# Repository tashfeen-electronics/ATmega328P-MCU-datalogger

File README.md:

# ATmega328P Data Logger — EEPROM + RTC

A compact, standalone data logging system built around the **ATmega328P** microcontroller, featuring **non-volatile EEPROM storage** and a **real-time clock (RTC)** for accurate timestamping. Designed for reliable, low-power, long-duration data collection without needing a constant computer connection.

---

## 🧠 Overview

This project logs sensor readings at fixed intervals, timestamps each entry using an RTC module, and stores the data permanently in EEPROM — surviving power loss, resets, and disconnects. It's built as a foundation for embedded data acquisition systems that need to run unattended in the field.

---

## ⚙️ Features

- 📌 Real-time timestamping using an external RTC module
- 💾 Persistent storage via EEPROM (data survives power cycles)
- 🔁 Configurable logging interval
- 🔋 Low power design, suitable for battery-powered deployment
- 📤 Simple data retrieval for post-processing and analysis
- 🧩 Modular code structure — easy to extend with new sensors

---

## 🛠️ Hardware Used

| Component            | Purpose                          |
|-----------------------|-----------------------------------|
| ATmega328P            | Core microcontroller / logic unit |
| RTC Module DS1337S    | Real-time timestamping   |
| EEPROM (external/internal) | Non-volatile data storage     |
| Sensor(s)              | Data source (analog/digital)     |
| Power supply / battery | Field-deployable operation       |

---

## 🧩 System Architecture

```
[ Sensor ] → [ ATmega328P ] → [ RTC: Timestamp ] → [ EEPROM: Store ]
                                      ↓
                              [ Data Retrieval / Analysis ]
```

**Flow:**
1. The MCU wakes up (or runs continuously) and triggers a reading at a set interval.
2. The RTC module provides the current date and time.
3. Sensor data is paired with the timestamp.
4. The combined record is written to EEPROM at the next available memory address.
5. Data can later be read out via serial interface for analysis.

---

## 📝 Design Notes

- **Memory management:** EEPROM write cycles are limited (~100,000 per cell), so writes are spaced out and address pointers are tracked to avoid unnecessary wear and overwrites.
- **Timestamp accuracy:** The RTC module runs independently of the MCU clock, so logged times remain accurate even after resets or brief power loss (backed by a coin-cell battery).
- **Data structure:** Each log entry is packed into a fixed-size record (timestamp + sensor value) to keep read/write operations predictable and efficient.
- **Power efficiency:** Sleep modes are used between logging intervals to minimize current draw for battery-powered, long-term deployments.
- **Scalability:** The logging interval, sensor type, and storage size are all designed to be easily reconfigurable without restructuring the core logic.

---

## 🚀 Practical Applications

- 🌱 **Agriculture** — soil moisture / temperature logging for irrigation planning
- 🌡️ **Environmental monitoring** — tracking temperature, humidity, or air quality over time
- 🏭 **Industrial systems** — recording equipment performance for predictive maintenance
- 🔬 **Research & academic projects** — collecting reliable, timestamped datasets in the field
- 🏠 **Home automation** — logging conditions for smart, data-driven decisions

---

## 📂 Data Retrieval

Logged data can be read out via the serial interface and exported for analysis in tools like Excel, Python (pandas), or MATLAB — enabling trend analysis, visualization, and further processing.

---

## 🔮 Future Improvements

- SD card integration for larger-scale storage
- Wireless data transmission (e.g. via ESP module)
- Multi-sensor support with dynamic record formatting
- Low-power sleep/wake scheduling for extended battery life

---

## 📜 License

This project is open for learning, modification, and reuse. Feel free to fork, build on it, and share improvements.

---

**Built as part of ongoing exploration in embedded systems and circuit design.**

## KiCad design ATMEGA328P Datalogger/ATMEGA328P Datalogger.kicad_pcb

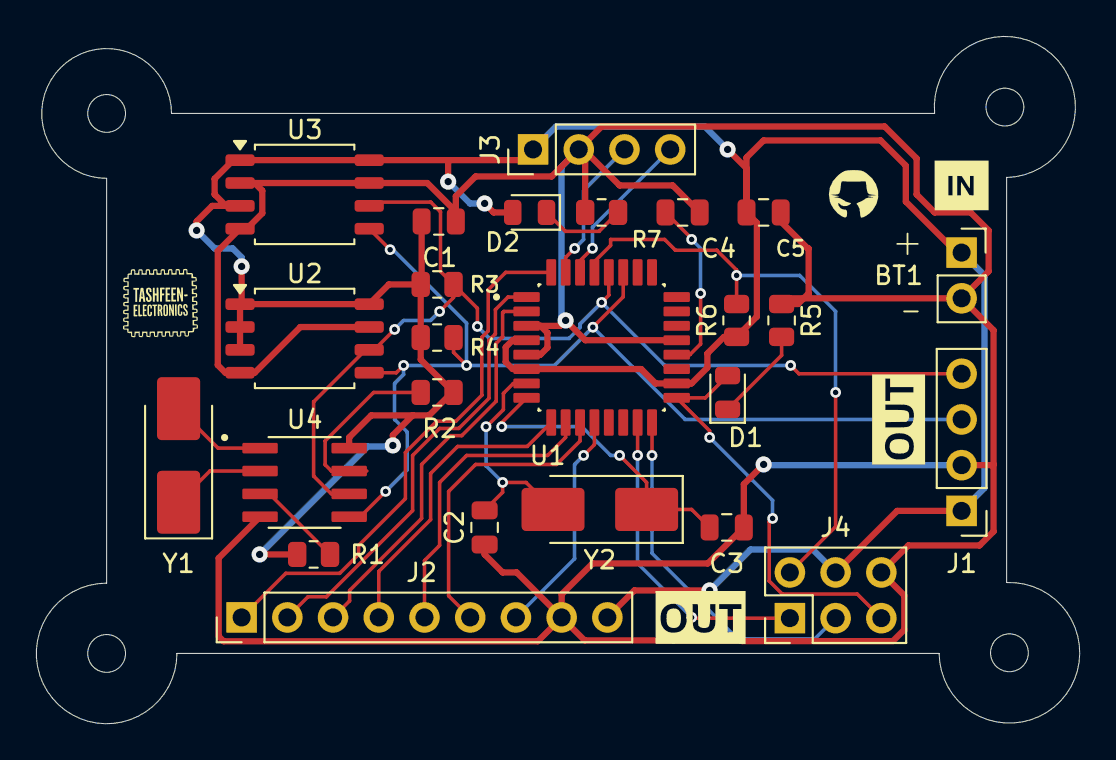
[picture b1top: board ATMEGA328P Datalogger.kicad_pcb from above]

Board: 2 copper layers, 58.0 x 38.2 mm, 30 parts (1 on the bottom side), 26 nets.

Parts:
.: LOGO
BT1: Battery; PinSocket_1x02_P2.54mm_Vertical
C1, C4: 0.1u; C_0805_2012Metric
C2, C3: 22p; C_0805_2012Metric
C5: 100n; C_0805_2012Metric
D1, D2: LED; LED_0805_2012Metric
H1, H2, H3, H4: MountingHole; MountingHole_2.1mm
J1, J3: Conn_01x04_Pin; PinHeader_1x04_P2.54mm_Vertical
J2: Conn_01x09_Pin; PinHeader_1x09_P2.54mm_Vertical
J4: Conn_02x03_Odd_Even; PinHeader_2x03_P2.54mm_Vertical
R1, R2, R6: 10k; R_0805_2012Metric
R3: 4.7k; R_0805_2012Metric
R4: 4.7; R_0805_2012Metric
R5, R7: 330; R_0805_2012Metric
U1: ATMEGA328P-AU; QFP80P900X900X120-32N
U2, U3: 24LC1025; SOIC-8_5.3x5.3mm_P1.27mm
U4: DS1337S_; SOIC127P600X175-8N
Y1: 32.768Khz; Crystal_SMD_5032-2Pin_5.0x3.2mm_HandSoldering
Y2: 16Mhz; Crystal_SMD_5032-2Pin_5.0x3.2mm_HandSoldering

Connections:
/D2: J2.1, U1.32 (PD2)
/D3: J2.2, U1.1 (PD3)
/D4: J2.3, U1.2 (PD4)
/D5: J2.4, U1.9 (PD5)
/D6: J2.5, U1.10 (PD6)
/D7: J2.6, U1.11 (PD7)
/D8: J2.7, U1.12 (PB0)
/MISO: J4.1, U1.15 (PB3)
/MOSI: J4.3, U1.16 (PB4)
/RESET: J4.2, R6.2, U1.29 (PC6/~RESET)
/RX: J3.3, U1.31 (PD1)
/SCK: D1.2 (A), J4.5, U1.17 (PB5)
/SCL: J1.4, R3.2, U1.28 (PC5), U2.6 (SCL), U3.6 (SCL), U4.6 (SCL)
/SDA: J1.3, R4.2, U1.27 (PC4), U2.5 (SDA), U3.5 (SDA), U4.5 (SDA)
/TX: J3.4, U1.30 (PD0)
GND: BT1.2 (-), C1.2, C2.1, C3.1, C4.2, C5.2, J1.2, J2.8, J3.2, J4.6, R5.1, R7.1, U1.3 (GND), U1.5 (GND), U1.21 (GND), U2.4 (GND), U2.7 (WP), U3.2 (A1), U3.4 (GND), U3.7 (WP), U4.4 (GND)
unnamed: D1.1 (K), R5.2
unnamed: D2.1 (K), R7.2
unnamed: C4.1, U1.20 (AREF)
unnamed: C2.2, U1.7 (PB6), Y2.2
unnamed: C3.2, U1.8 (PB7), Y2.1
unnamed: R2.1, U4.7 (SQW/~INT)
unnamed: U4.1 (X1), Y1.2
unnamed: U4.2 (X2), Y1.1
unnamed: R1.2, U4.3 (~INTA)
VCC: BT1.1 (+), C1.1, C5.1, D2.2 (A), J1.1, J2.9, J3.1, J4.4, R1.1, R2.2, R3.1, R4.1, R6.1, U1.4 (VCC), U1.6 (VCC), U1.18 (AVCC), U2.1 (A0), U2.2 (A1), U2.3 (A2), U2.8 (VCC), U3.1 (A0), U3.3 (A2), U3.8 (VCC), U4.8 (VCC)
